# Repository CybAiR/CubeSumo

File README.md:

# CubeSumo - 🚧 Work in Progress
Minisumo robot built for sumo battles, equipped with multiple sensors for reliable navigation and opponent detection.

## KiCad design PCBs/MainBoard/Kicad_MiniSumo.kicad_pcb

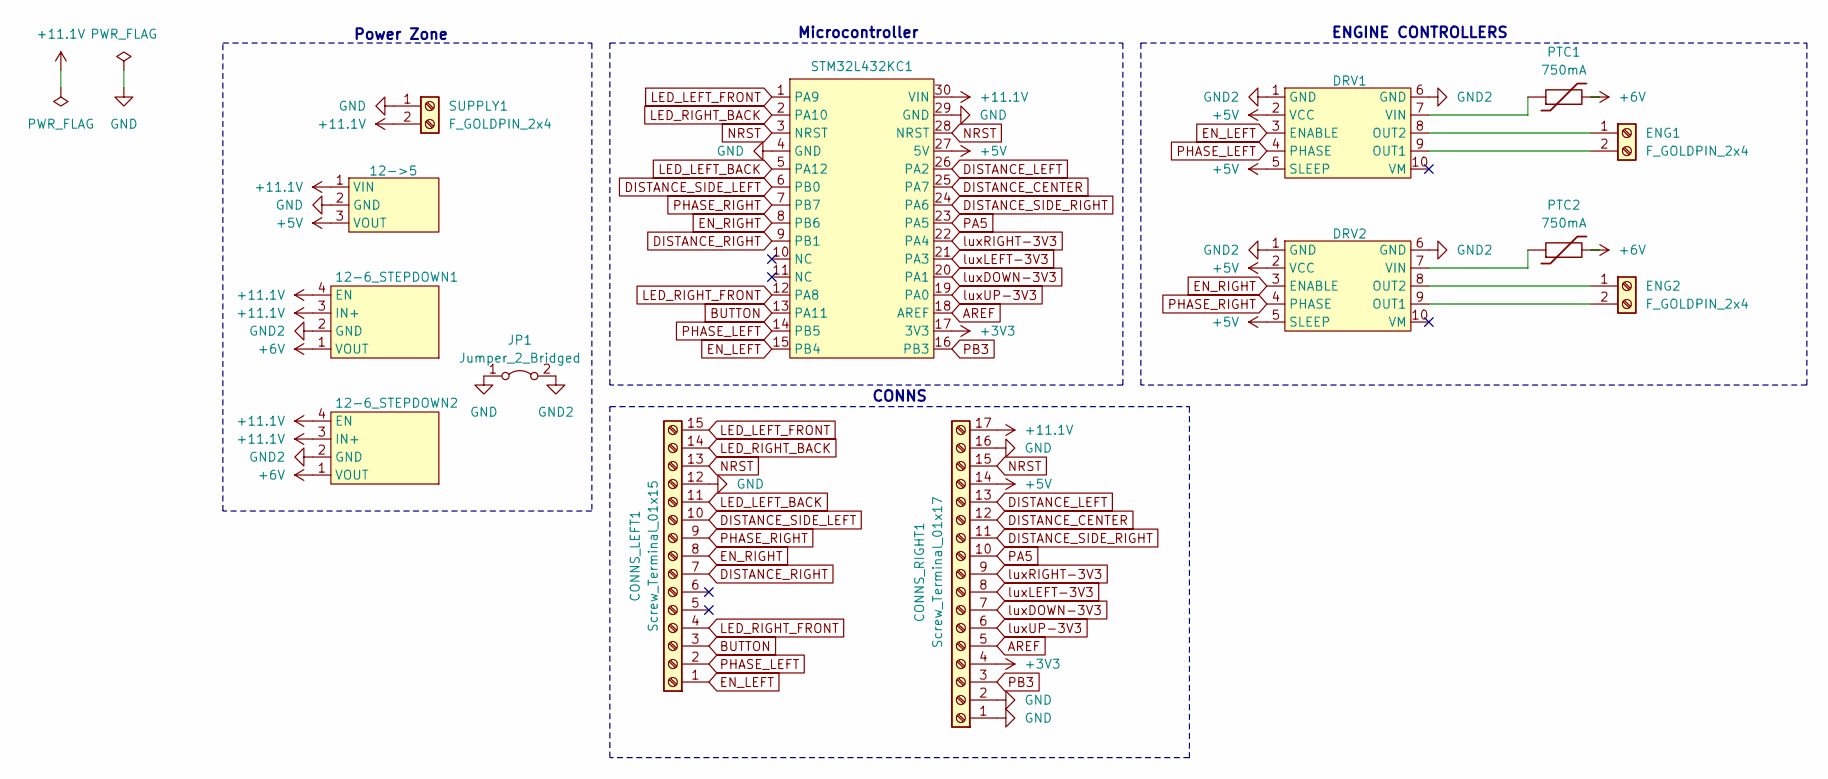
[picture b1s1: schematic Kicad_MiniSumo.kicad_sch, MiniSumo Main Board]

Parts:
12-6_STEPDOWN1, 12-6_STEPDOWN2: DC-DC Step-Down 0.8-17V 3A
12->5: S7V7F5
CONNS_LEFT1: Screw_Terminal_01x15; PinSocket_1x15_P2.54mm_Vertical
CONNS_RIGHT1: Screw_Terminal_01x17; PinSocket_1x17_P2.54mm_Vertical
DRV1, DRV2: DRV8838
ENG1, ENG2: F_GOLDPIN_2x4; PinSocket_2x02_P2.54mm_Vertical
JP1: Jumper_2_Bridged; SolderJumper-2_P1.3mm_Bridged2Bar_Pad1.0x1.5mm
PTC1, PTC2: 750mA; Fuse_1812_4532Metric_Pad1.30x3.40mm_HandSolder
STM32L432KC1: MODULE_NUCLEO-L432KC
SUPPLY1: F_GOLDPIN_2x4; PinSocket_2x02_P2.54mm_Vertical

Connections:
+3V3: CONNS_RIGHT1.4, STM32L432KC1.17 (3V3)
+5V: 12->5.3 (VOUT), CONNS_RIGHT1.14, DRV1.2 (VCC), DRV1.5 (SLEEP), DRV2.2 (VCC), DRV2.5 (SLEEP), STM32L432KC1.27 (5V)
+6V: 12-6_STEPDOWN1.1 (VOUT), 12-6_STEPDOWN2.1 (VOUT), PTC1.2, PTC2.2
+11.1V: 12-6_STEPDOWN1.3 (IN+), 12-6_STEPDOWN1.4 (EN), 12-6_STEPDOWN2.3 (IN+), 12-6_STEPDOWN2.4 (EN), 12->5.1 (VIN), CONNS_RIGHT1.17, STM32L432KC1.30 (VIN), SUPPLY1.2
AREF: CONNS_RIGHT1.5, STM32L432KC1.18 (AREF)
BUTTON: CONNS_LEFT1.3, STM32L432KC1.13 (PA11); also elsewhere on the board
DISTANCE_CENTER: CONNS_RIGHT1.12, STM32L432KC1.25 (PA7)
DISTANCE_LEFT: CONNS_RIGHT1.13, STM32L432KC1.26 (PA2)
DISTANCE_RIGHT: CONNS_LEFT1.7, STM32L432KC1.9 (PB1); also elsewhere on the board
DISTANCE_SIDE_LEFT: CONNS_LEFT1.10, STM32L432KC1.6 (PB0); also elsewhere on the board
DISTANCE_SIDE_RIGHT: CONNS_RIGHT1.11, STM32L432KC1.24 (PA6)
EN_LEFT: CONNS_LEFT1.1, DRV1.3 (ENABLE), STM32L432KC1.15 (PB4); also elsewhere on the board
EN_RIGHT: CONNS_LEFT1.8, DRV2.3 (ENABLE), STM32L432KC1.8 (PB6); also elsewhere on the board
GND: 12->5.2 (GND), CONNS_LEFT1.12, CONNS_RIGHT1.1, CONNS_RIGHT1.2, CONNS_RIGHT1.16, JP1.1 (A), STM32L432KC1.4 (GND), STM32L432KC1.29 (GND), SUPPLY1.1; also elsewhere on the board
GND2: 12-6_STEPDOWN1.2 (GND), 12-6_STEPDOWN2.2 (GND), DRV1.1 (GND), DRV1.6 (GND), DRV2.1 (GND), DRV2.6 (GND), JP1.2 (B)
LED_LEFT_BACK: CONNS_LEFT1.11, STM32L432KC1.5 (PA12); also elsewhere on the board
LED_LEFT_FRONT: CONNS_LEFT1.15, STM32L432KC1.1 (PA9); also elsewhere on the board
LED_RIGHT_BACK: CONNS_LEFT1.14, STM32L432KC1.2 (PA10); also elsewhere on the board
LED_RIGHT_FRONT: CONNS_LEFT1.4, STM32L432KC1.12 (PA8); also elsewhere on the board
NRST: CONNS_LEFT1.13, CONNS_RIGHT1.15, STM32L432KC1.3 (NRST), STM32L432KC1.28 (NRST); also elsewhere on the board
unnamed: DRV1.9 (OUT1), ENG1.2
unnamed: DRV1.8 (OUT2), ENG1.1
unnamed: DRV1.7 (VIN), PTC1.1
unnamed: DRV2.9 (OUT1), ENG2.2
unnamed: DRV2.8 (OUT2), ENG2.1
unnamed: DRV2.7 (VIN), PTC2.1
PA5: CONNS_RIGHT1.10, STM32L432KC1.23 (PA5)
PB3: CONNS_RIGHT1.3, STM32L432KC1.16 (PB3)
PHASE_LEFT: CONNS_LEFT1.2, DRV1.4 (PHASE), STM32L432KC1.14 (PB5); also elsewhere on the board
PHASE_RIGHT: CONNS_LEFT1.9, DRV2.4 (PHASE), STM32L432KC1.7 (PB7); also elsewhere on the board
luxDOWN-3V3: CONNS_RIGHT1.7, STM32L432KC1.20 (PA1)
luxLEFT-3V3: CONNS_RIGHT1.8, STM32L432KC1.21 (PA3)
luxRIGHT-3V3: CONNS_RIGHT1.9, STM32L432KC1.22 (PA4)
luxUP-3V3: CONNS_RIGHT1.6, STM32L432KC1.19 (PA0)

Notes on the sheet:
CONNS
Microcontroller
ENGINE CONTROLLERS
Power Zone

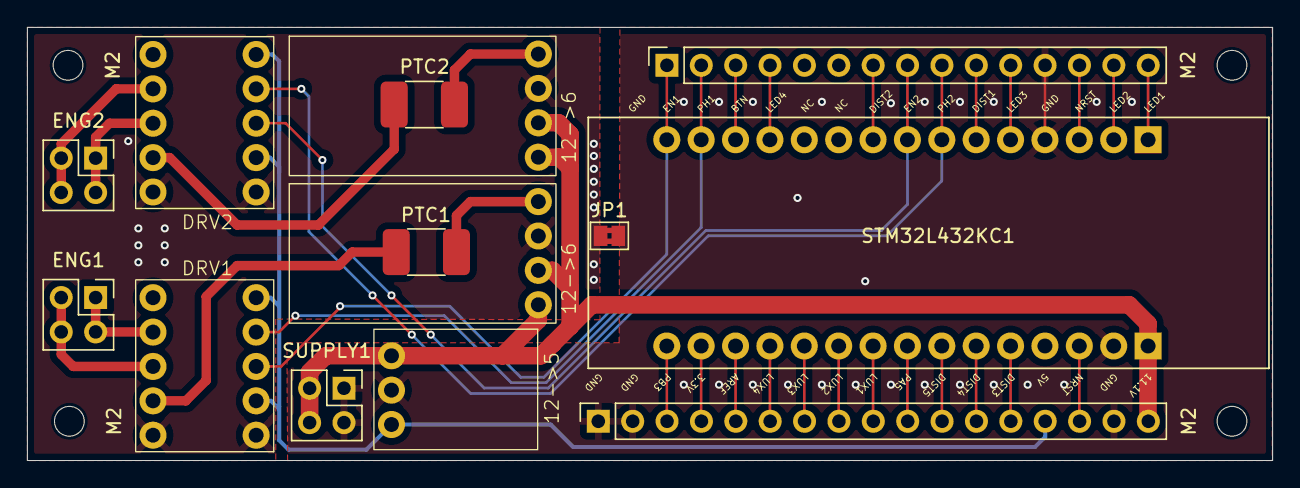
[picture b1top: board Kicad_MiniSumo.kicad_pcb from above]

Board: 2 copper layers, 92.0 x 32.0 mm, 18 parts (0 on the bottom side), 34 nets.

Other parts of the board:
J1: Screw_Terminal_01x15; PinSocket_1x15_P2.54mm_Vertical
M2, M2#2, M2#3, M2#4: MountingHole_2.2mm_M2

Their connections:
BUTTON: J1.3; also elsewhere on the board
DISTANCE_RIGHT: J1.7; also elsewhere on the board
DISTANCE_SIDE_LEFT: J1.10; also elsewhere on the board
EN_LEFT: J1.1; also elsewhere on the board
EN_RIGHT: J1.8; also elsewhere on the board
GND: J1.12; also elsewhere on the board
LED_LEFT_BACK: J1.11; also elsewhere on the board
LED_LEFT_FRONT: J1.15; also elsewhere on the board
LED_RIGHT_BACK: J1.14; also elsewhere on the board
LED_RIGHT_FRONT: J1.4; also elsewhere on the board
NRST: J1.13; also elsewhere on the board
PHASE_LEFT: J1.2; also elsewhere on the board
PHASE_RIGHT: J1.9; also elsewhere on the board

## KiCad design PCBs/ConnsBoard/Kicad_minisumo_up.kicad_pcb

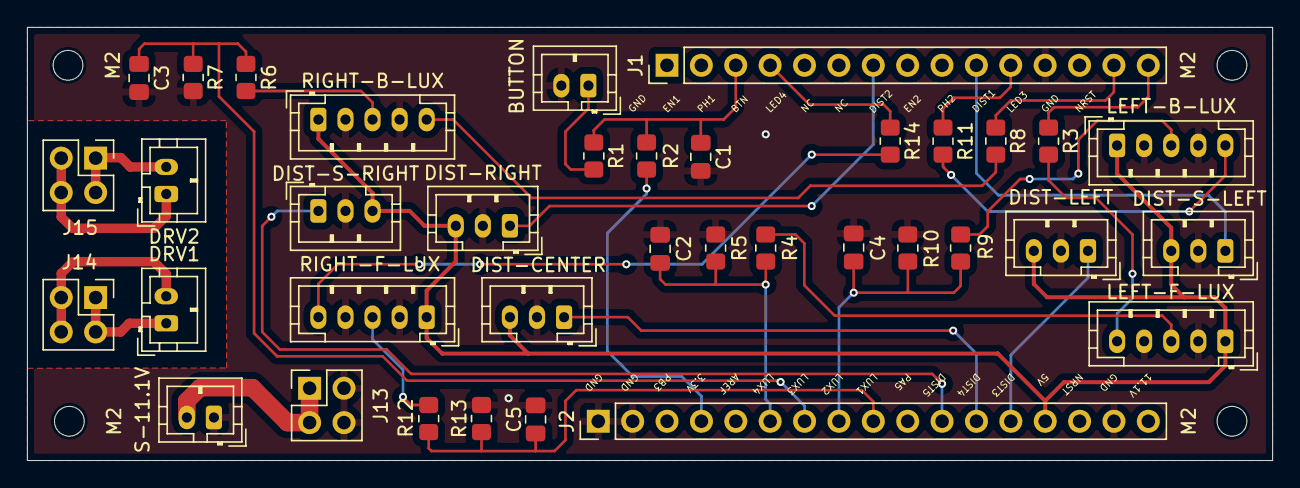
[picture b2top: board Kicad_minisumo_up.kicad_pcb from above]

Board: 2 copper layers, 92.0 x 32.0 mm, 41 parts (0 on the bottom side), 32 nets.

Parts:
BUTTON: button; JST_PH_B2B-PH-K_1x02_P2.00mm_Vertical
C1: 100nF; C_0805_2012Metric_Pad1.18x1.45mm_HandSolder
C2, C3, C4, C5: 100NF; C_0805_2012Metric_Pad1.18x1.45mm_HandSolder
DIST-CENTER: distance center; JST_PH_B3B-PH-K_1x03_P2.00mm_Vertical
DIST-LEFT: distance_left; JST_PH_B3B-PH-K_1x03_P2.00mm_Vertical
DIST-RIGHT: distance_right; JST_PH_B3B-PH-K_1x03_P2.00mm_Vertical
DIST-S-LEFT: distance_side_left; JST_PH_B3B-PH-K_1x03_P2.00mm_Vertical
DIST-S-RIGHT: distance_side_right; JST_PH_B3B-PH-K_1x03_P2.00mm_Vertical
DRV1, DRV2: JST; JST_PH_B2B-PH-K_1x02_P2.00mm_Vertical
J1: Screw_Terminal_01x15; PinHeader_1x15_P2.54mm_Vertical
J2: Screw_Terminal_01x17; PinHeader_1x17_P2.54mm_Vertical
J13, J14, J15: screw; PinHeader_2x02_P2.54mm_Vertical
LEFT-B-LUX: lux_left_back; JST_PH_B5B-PH-K_1x05_P2.00mm_Vertical
LEFT-F-LUX: lux_left_front; JST_PH_B5B-PH-K_1x05_P2.00mm_Vertical
M2, M2#2, M2#3, M2#4: MountingHole_2.2mm_M2
R1: 1k; R_0805_2012Metric_Pad1.20x1.40mm_HandSolder
R2, R4, R6, R9, R12: 10k; R_0805_2012Metric_Pad1.20x1.40mm_HandSolder
R3, R8, R11, R14: 100; R_0805_2012Metric_Pad1.20x1.40mm_HandSolder
R5, R7, R10, R13: 20k; R_0805_2012Metric_Pad1.20x1.40mm_HandSolder
RIGHT-B-LUX: lux_right_back; JST_PH_B5B-PH-K_1x05_P2.00mm_Vertical
RIGHT-F-LUX: lux_right_front; JST_PH_B5B-PH-K_1x05_P2.00mm_Vertical
S-11.1V: JST; JST_PH_B2B-PH-K_1x02_P2.00mm_Vertical

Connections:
+3V3: J2.4, R2.1
+5V: DIST-CENTER.3, DIST-LEFT.3, DIST-RIGHT.3, DIST-S-LEFT.3, DIST-S-RIGHT.3, J2.14, LEFT-B-LUX.1, LEFT-F-LUX.1, RIGHT-B-LUX.1, RIGHT-F-LUX.1
+11.1V: J13.2, S-11.1V.2
BUTTON: C1.1, J1.3, R1.1, R2.2
DISTANCE_CENTER: DIST-CENTER.1, J2.12
DISTANCE_LEFT: DIST-LEFT.1, J2.13
DISTANCE_RIGHT: DIST-RIGHT.1, J1.7
DISTANCE_SIDE_LEFT: DIST-S-LEFT.1, J1.10
DISTANCE_SIDE_RIGHT: DIST-S-RIGHT.1, J2.11
DRV1_OUT1: DRV1.2, J14.2
DRV1_OUT2: DRV1.1, J14.1
DRV2_OUT1: DRV2.2, J15.2
DRV2_OUT2: DRV2.1, J15.1
GND: BUTTON.2, C1.2, C2.2, C3.2, C4.2, C5.2, DIST-CENTER.2, DIST-LEFT.2, DIST-RIGHT.2, DIST-S-LEFT.2, DIST-S-RIGHT.2, J1.12, J2.1, J2.2, J2.16, J13.1, LEFT-B-LUX.2, LEFT-B-LUX.4, LEFT-F-LUX.2, LEFT-F-LUX.4, R5.2, R7.2, R10.2, R13.2, RIGHT-B-LUX.2, RIGHT-B-LUX.4, RIGHT-F-LUX.2, RIGHT-F-LUX.4, S-11.1V.1
LED_LEFT_BACK: J1.11, R11.1
LED_LEFT_FRONT: J1.15, R3.1
LED_RIGHT_BACK: J1.14, R8.1
LED_RIGHT_FRONT: J1.4, R14.1
NRST: J1.13, J2.15
unnamed: BUTTON.1, R1.2
unnamed: LEFT-F-LUX.5, R3.2
unnamed: R8.2, RIGHT-B-LUX.5
unnamed: LEFT-B-LUX.5, R11.2
unnamed: R14.2, RIGHT-F-LUX.5
luxDOWN-3V3: C3.1, J2.7, R6.2, R7.1
luxDOWN-5V: R6.1, RIGHT-B-LUX.3
luxLEFT-3V3: C4.1, J2.8, R9.2, R10.1
luxLEFT-5V: LEFT-B-LUX.3, R9.1
luxRIGHT-3V3: C5.1, J2.9, R12.2, R13.1
luxRIGHT-5V: R12.1, RIGHT-F-LUX.3
luxUP-3V3: C2.1, J2.6, R4.2, R5.1
luxUP-5V: LEFT-F-LUX.3, R4.1

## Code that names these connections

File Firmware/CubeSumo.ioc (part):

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Mcu.Name=STM32L432K(B-C)Ux
Mcu.Package=UFQFPN32
Mcu.UserName=STM32L432KCUx
PA0.GPIOParameters=GPIO_Label
PA0.GPIO_Label=LUX3
PA0.Signal=ADCx_IN5
PA1.GPIOParameters=GPIO_Label
PA1.GPIO_Label=LUX2
PA1.Signal=ADCx_IN6
PA10.GPIOParameters=GPIO_PuPd,GPIO_Label
PA10.GPIO_Label=LED2
PA10.GPIO_PuPd=GPIO_PULLDOWN
PA10.Signal=GPIO_Output
PA11.GPIOParameters=GPIO_Label
PA11.GPIO_Label=BTN
PA11.Signal=GPIO_Input
PA12.GPIOParameters=GPIO_PuPd,GPIO_Label
PA12.GPIO_Label=LED4
PA12.GPIO_PuPd=GPIO_PULLDOWN
PA12.Signal=GPIO_Output
PA13\ (JTMS-SWDIO).GPIOParameters=GPIO_Label
PA13\ (JTMS-SWDIO).GPIO_Label=SWDIO
PA13\ (JTMS-SWDIO).Mode=Serial_Wire
PA13\ (JTMS-SWDIO).Signal=SYS_JTMS-SWDIO
PA14\ (JTCK-SWCLK).GPIOParameters=GPIO_Label
PA14\ (JTCK-SWCLK).GPIO_Label=SWCLK
PA14\ (JTCK-SWCLK).Mode=Serial_Wire
PA14\ (JTCK-SWCLK).Signal=SYS_JTCK-SWCLK
PA2.Signal=ADCx_IN7
PA3.GPIOParameters=GPIO_Label
PA3.GPIO_Label=LUX4
PA3.Signal=ADCx_IN8
PA4.GPIOParameters=GPIO_Label
PA4.GPIO_Label=LUX1
PA4.Signal=ADCx_IN9
PA6.Signal=ADCx_IN11
PA7.Signal=ADCx_IN12
PA8.GPIOParameters=GPIO_PuPd,GPIO_Label
PA8.GPIO_Label=LED1
PA8.GPIO_PuPd=GPIO_PULLDOWN
PA8.Signal=GPIO_Output
PA9.GPIOParameters=GPIO_PuPd,GPIO_Label
PA9.GPIO_Label=LED3
PA9.GPIO_PuPd=GPIO_PULLDOWN
PA9.Signal=GPIO_Output
PB0.Signal=ADCx_IN15
PB1.Signal=ADCx_IN16
PB3\ (JTDO-TRACESWO).GPIOParameters=GPIO_PuPd,GPIO_Label
PB3\ (JTDO-TRACESWO).GPIO_Label=LD3 [Green]
PB3\ (JTDO-TRACESWO).GPIO_PuPd=GPIO_NOPULL
PB3\ (JTDO-TRACESWO).Signal=GPIO_Output
PB4\ (NJTRST).GPIOParameters=GPIO_PuPd,GPIO_Label
PB4\ (NJTRST).GPIO_Label=EN_LEFT
PB4\ (NJTRST).GPIO_PuPd=GPIO_PULLDOWN
PB4\ (NJTRST).Signal=GPIO_Output
PB5.GPIOParameters=GPIO_PuPd,GPIO_Label
PB5.GPIO_Label=PHASE_LEFT
PB5.GPIO_PuPd=GPIO_PULLDOWN
PB5.Signal=GPIO_Output
PB6.GPIOParameters=GPIO_PuPd,GPIO_Label
PB6.GPIO_Label=EN_RIGHT
PB6.GPIO_PuPd=GPIO_PULLDOWN
PB6.Signal=GPIO_Output
PB7.GPIOParameters=GPIO_PuPd,GPIO_Label
PB7.GPIO_Label=PHASE_RIGHT
PB7.GPIO_PuPd=GPIO_PULLDOWN
PB7.Signal=GPIO_Output
PC14-OSC32_IN\ (PC14).Mode=LSE-External-Oscillator
PC14-OSC32_IN\ (PC14).Signal=RCC_OSC32_IN
PC15-OSC32_OUT\ (PC15).Mode=LSE-External-Oscillator
PC15-OSC32_OUT\ (PC15).Signal=RCC_OSC32_OUT
RCC.HSE_VALUE=8000000
RCC.SYSCLKFreq_VALUE=32000000
RCC.SYSCLKSource=RCC_SYSCLKSOURCE_PLLCLK
board=NUCLEO-L432KC
boardIOC=true

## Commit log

2025-07-20 Created .gitignore file and started ignoring kicad useless files
2025-07-20 Added Main Board PCB project
2025-07-20 Added Conns Board PCB project
2025-07-20 Added images for README
2025-07-20 Modified README file to show images of the project
2025-07-21 Modified .gitignore to ignore files from new project firmware folder
2025-07-21 Added empty stm32 Cmake project for VScode with STM32 Code extension
2025-07-21 Added sensors reading and storing them in separate variables
2025-07-24 Added button usage handling
2025-07-27 Added all necessary functions for digital PWM creation and added functions for moving robot forward and backward
2025-07-27 Modified .gitignore file to ignore ninja files
2025-07-27 Created new movement library and moved all functions connected with movement to this library
2025-07-27 Added functions for single wheel movement
2025-07-27 Fixed direction naming for single wheel movements in movement library
2025-07-27 Added functions for robot rotating and fixed direction naming for rotating movement
2025-07-27 Added LEDs control function
2025-07-27 Added state machine template - ready to work on logic
2025-07-28 Added line detection handling functionality
2025-07-28 Added enemy robot basic detection - finished search state
2025-08-18 Changed rotate and backward time defines for better action after line detection
2025-08-18 Change light sensor measurements variables names
2025-08-18 Change distance sensor measurements variables names
2026-02-15 Increased pad and hole diameters for the goldpins in the Main Board
2026-02-15 Rotate supply connector to match supply wires colors
2026-02-15 Update ground pour on the Main Board before genereting GERBER files
2026-02-15 Update ground pour on the Conns Board before genereting GERBER files
2026-02-15 Added GERBER files into .gitignore
2026-02-15 Changed ground pour connection with pads into thermal connection
2026-04-06 fix: fix full GND filling into thermal
2026-04-06 fix: remove already fixed comments
2026-04-06 fix: add comment about changing the uC
